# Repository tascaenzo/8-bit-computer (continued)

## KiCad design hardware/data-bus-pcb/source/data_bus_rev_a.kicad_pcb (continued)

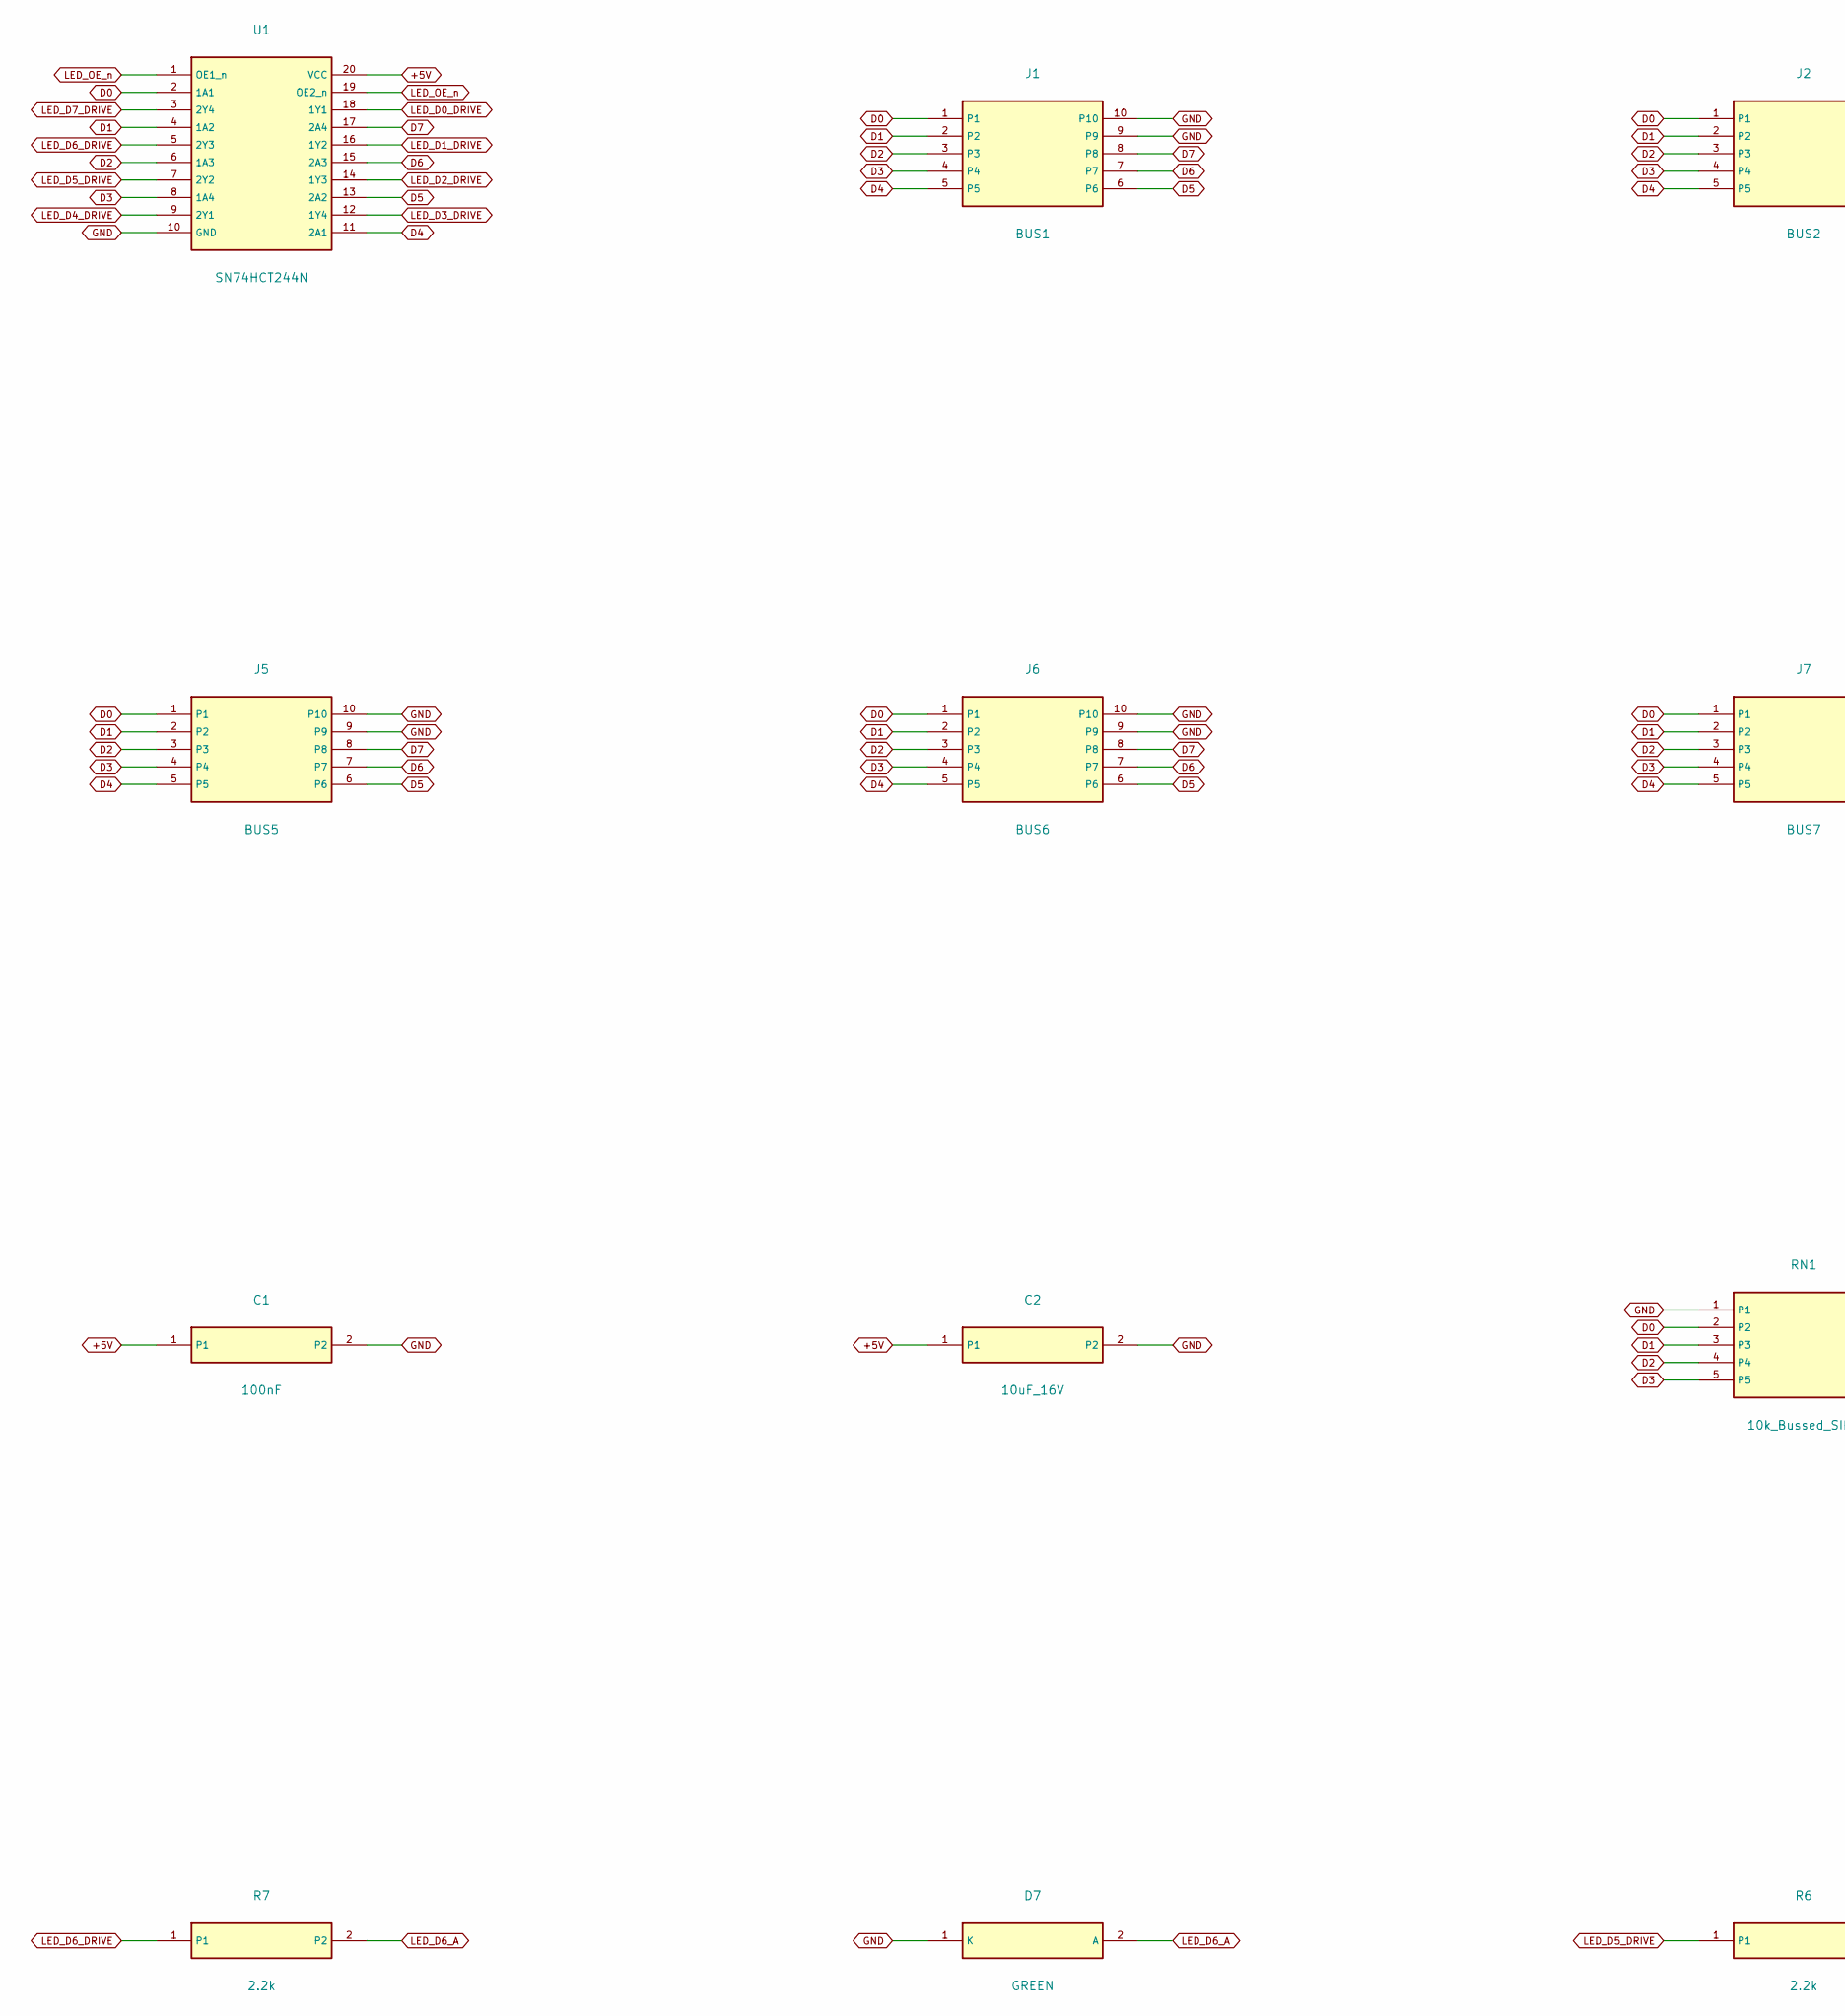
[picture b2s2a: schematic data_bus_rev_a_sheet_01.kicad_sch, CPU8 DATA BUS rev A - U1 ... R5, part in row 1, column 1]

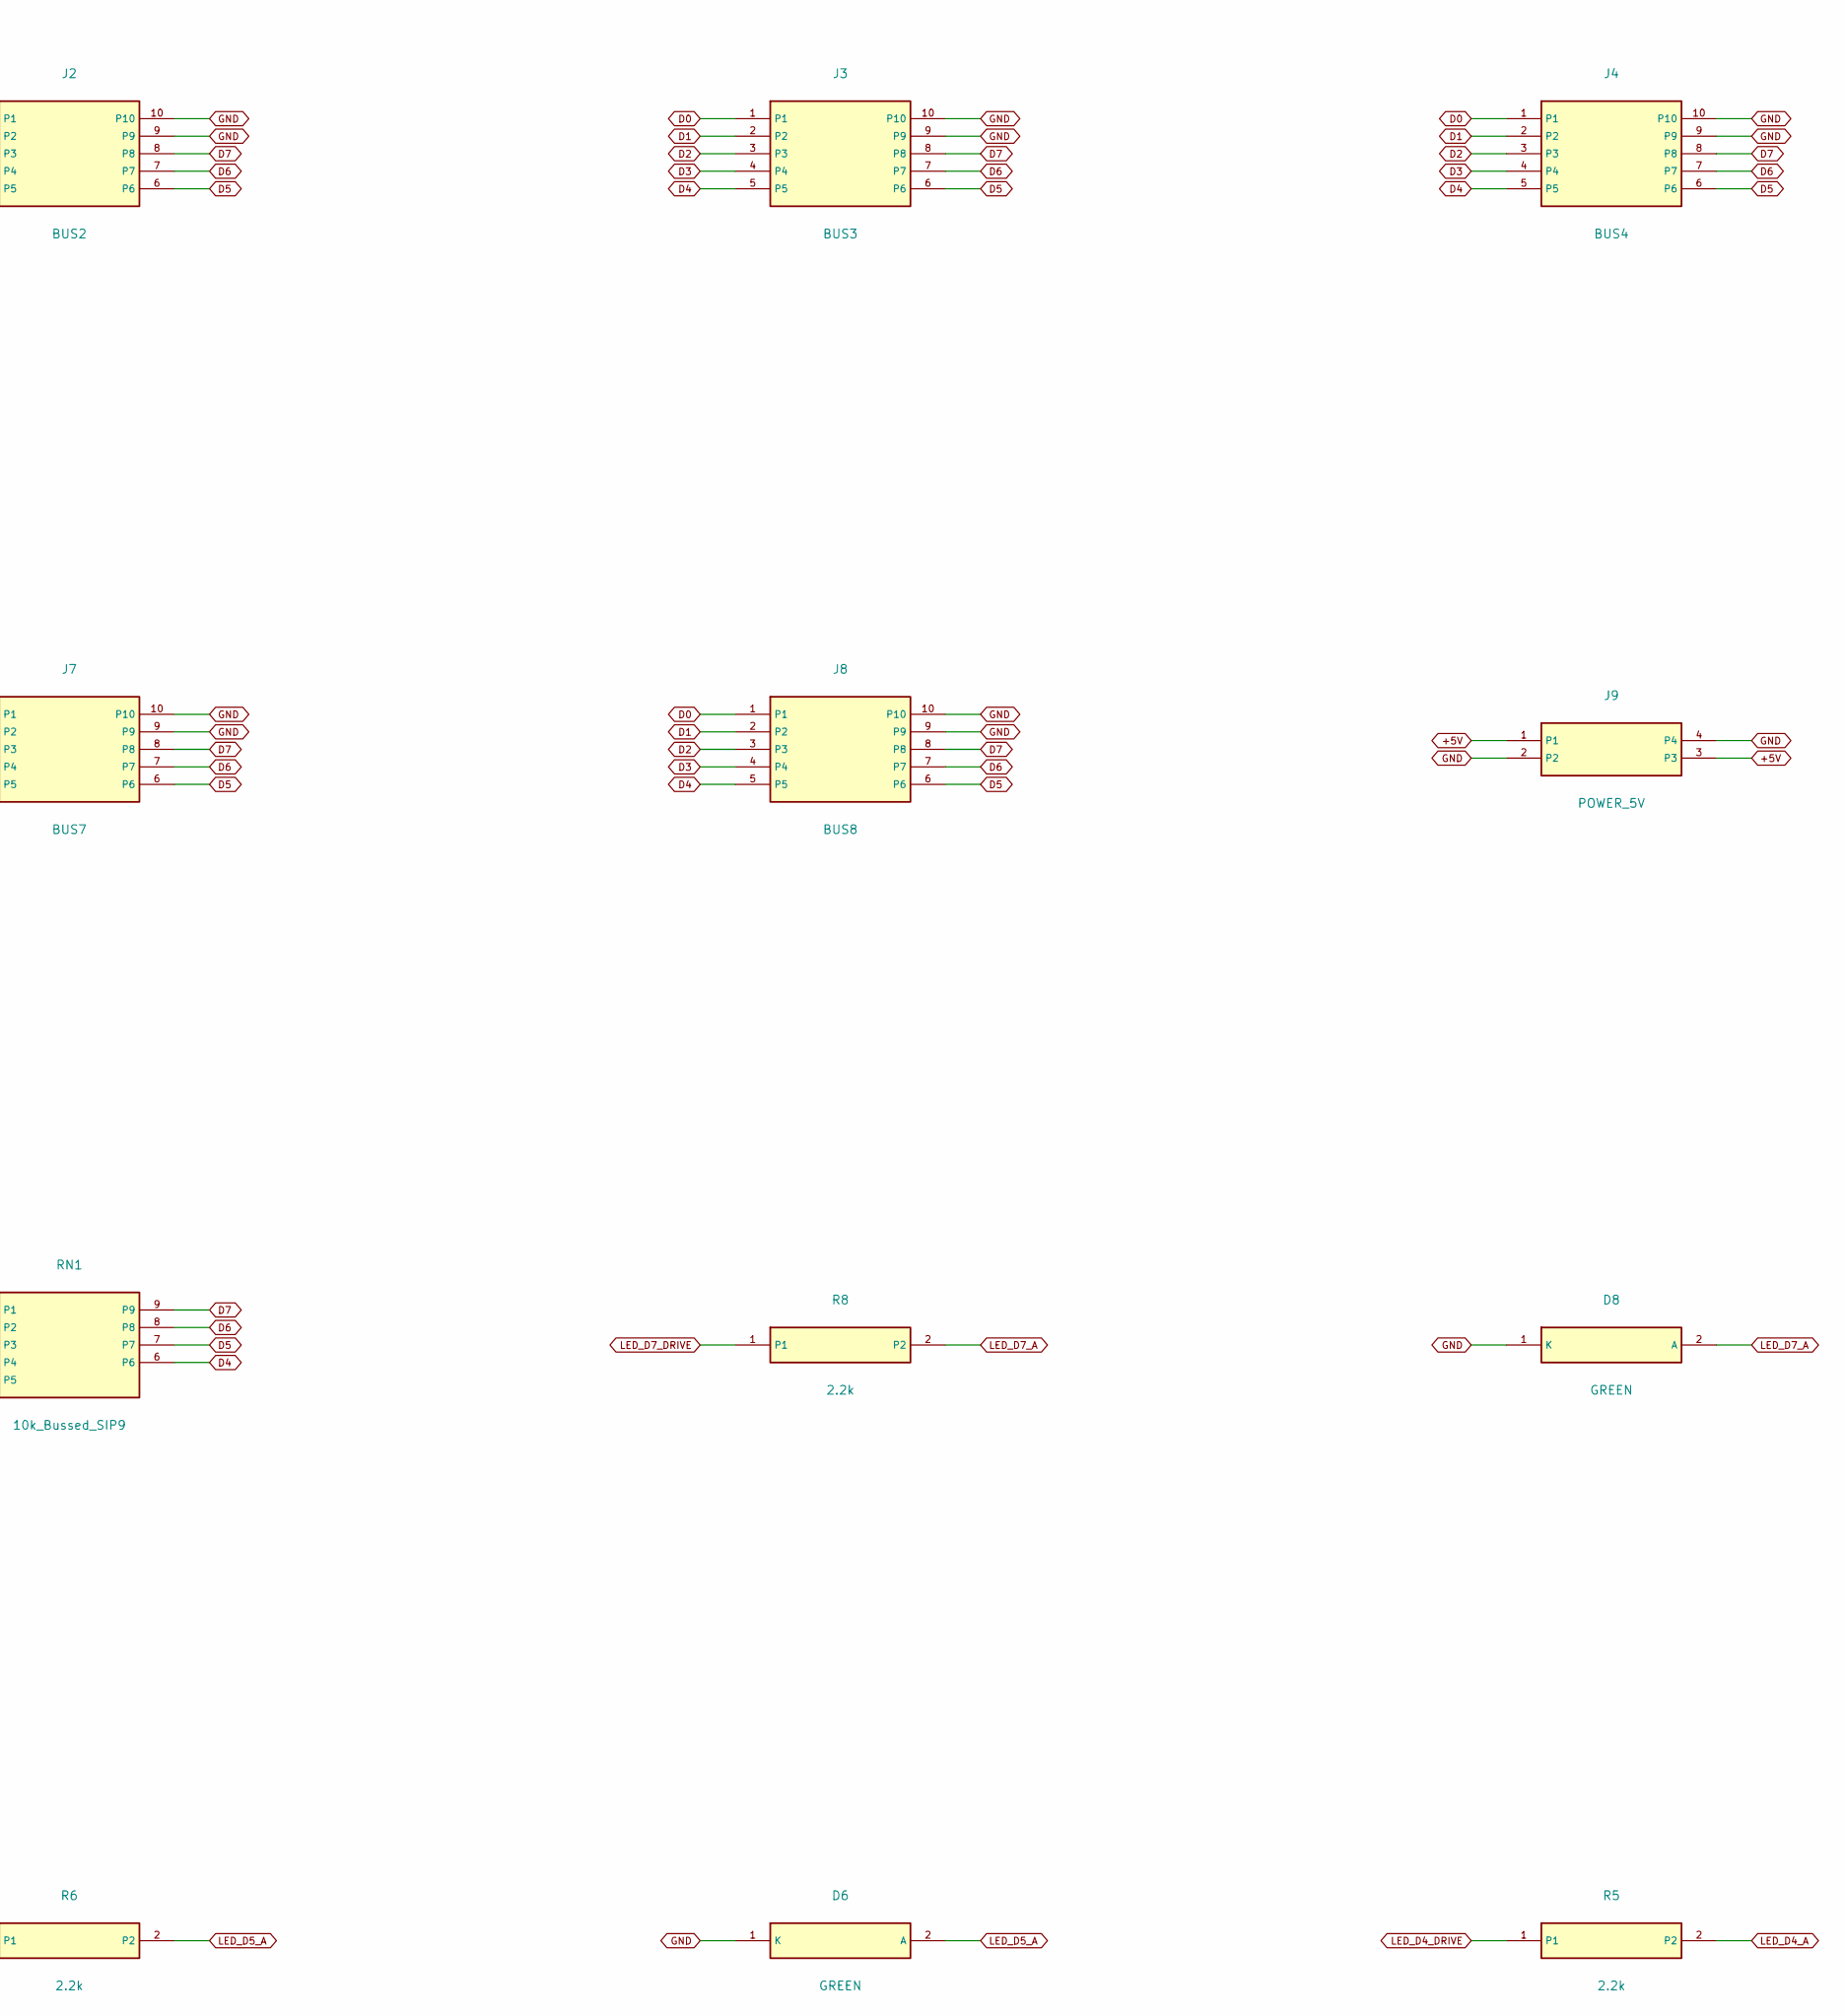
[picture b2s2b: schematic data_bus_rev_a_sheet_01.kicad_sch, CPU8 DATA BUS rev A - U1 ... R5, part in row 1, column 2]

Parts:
C1: 100nF; C_Disc_P2.50mm
C2: 10uF_16V; C_Radial_P2.50mm
D6, D7, D8: GREEN; LED_D3.0mm_P2.54mm_Vertical
J1: BUS1; Header_2x5_P2.54mm
J2: BUS2; Header_2x5_P2.54mm
J3: BUS3; Header_2x5_P2.54mm
J4: BUS4; Header_2x5_P2.54mm
J5: BUS5; Header_2x5_P2.54mm
J6: BUS6; Header_2x5_P2.54mm
J7: BUS7; Header_2x5_P2.54mm
J8: BUS8; Header_2x5_P2.54mm
J9: POWER_5V; Header_2x2_P2.54mm
R5, R6, R7, R8: 2.2k; R_Axial_P7.62mm
RN1: 10k_Bussed_SIP9; SIP-9_P2.54mm
U1: SN74HCT244N; DIP-20_W7.62mm

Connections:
+5V: C1.1, C2.1, J9.1, J9.3, U1.20 (VCC); also elsewhere on the board
D0: J1.1, J2.1, J3.1, J4.1, J5.1, J6.1, J7.1, J8.1, RN1.2, U1.2 (1A1)
D1: J1.2, J2.2, J3.2, J4.2, J5.2, J6.2, J7.2, J8.2, RN1.3, U1.4 (1A2)
D2: J1.3, J2.3, J3.3, J4.3, J5.3, J6.3, J7.3, J8.3, RN1.4, U1.6 (1A3)
D3: J1.4, J2.4, J3.4, J4.4, J5.4, J6.4, J7.4, J8.4, RN1.5, U1.8 (1A4)
D4: J1.5, J2.5, J3.5, J4.5, J5.5, J6.5, J7.5, J8.5, RN1.6, U1.11 (2A1)
D5: J1.6, J2.6, J3.6, J4.6, J5.6, J6.6, J7.6, J8.6, RN1.7, U1.13 (2A2)
D6: J1.7, J2.7, J3.7, J4.7, J5.7, J6.7, J7.7, J8.7, RN1.8, U1.15 (2A3)
D7: J1.8, J2.8, J3.8, J4.8, J5.8, J6.8, J7.8, J8.8, RN1.9, U1.17 (2A4)
GND: C1.2, C2.2, D6.1 (K), D7.1 (K), D8.1 (K), J1.9, J1.10, J2.9, J2.10, J3.9, J3.10, J4.9, J4.10, J5.9, J5.10, J6.9, J6.10, J7.9, J7.10, J8.9, J8.10, J9.2, J9.4, RN1.1, U1.10 (GND); also elsewhere on the board
LED_D0_DRIVE: U1.18 (1Y1); also elsewhere on the board
LED_D1_DRIVE: U1.16 (1Y2); also elsewhere on the board
LED_D2_DRIVE: U1.14 (1Y3); also elsewhere on the board
LED_D3_DRIVE: U1.12 (1Y4); also elsewhere on the board
LED_D4_A: R5.2; also elsewhere on the board
LED_D4_DRIVE: R5.1, U1.9 (2Y1)
LED_D5_A: D6.2 (A), R6.2
LED_D5_DRIVE: R6.1, U1.7 (2Y2)
LED_D6_A: D7.2 (A), R7.2
LED_D6_DRIVE: R7.1, U1.5 (2Y3)
LED_D7_A: D8.2 (A), R8.2
LED_D7_DRIVE: R8.1, U1.3 (2Y4)
LED_OE_n: U1.1 (OE1_n), U1.19 (OE2_n); also elsewhere on the board

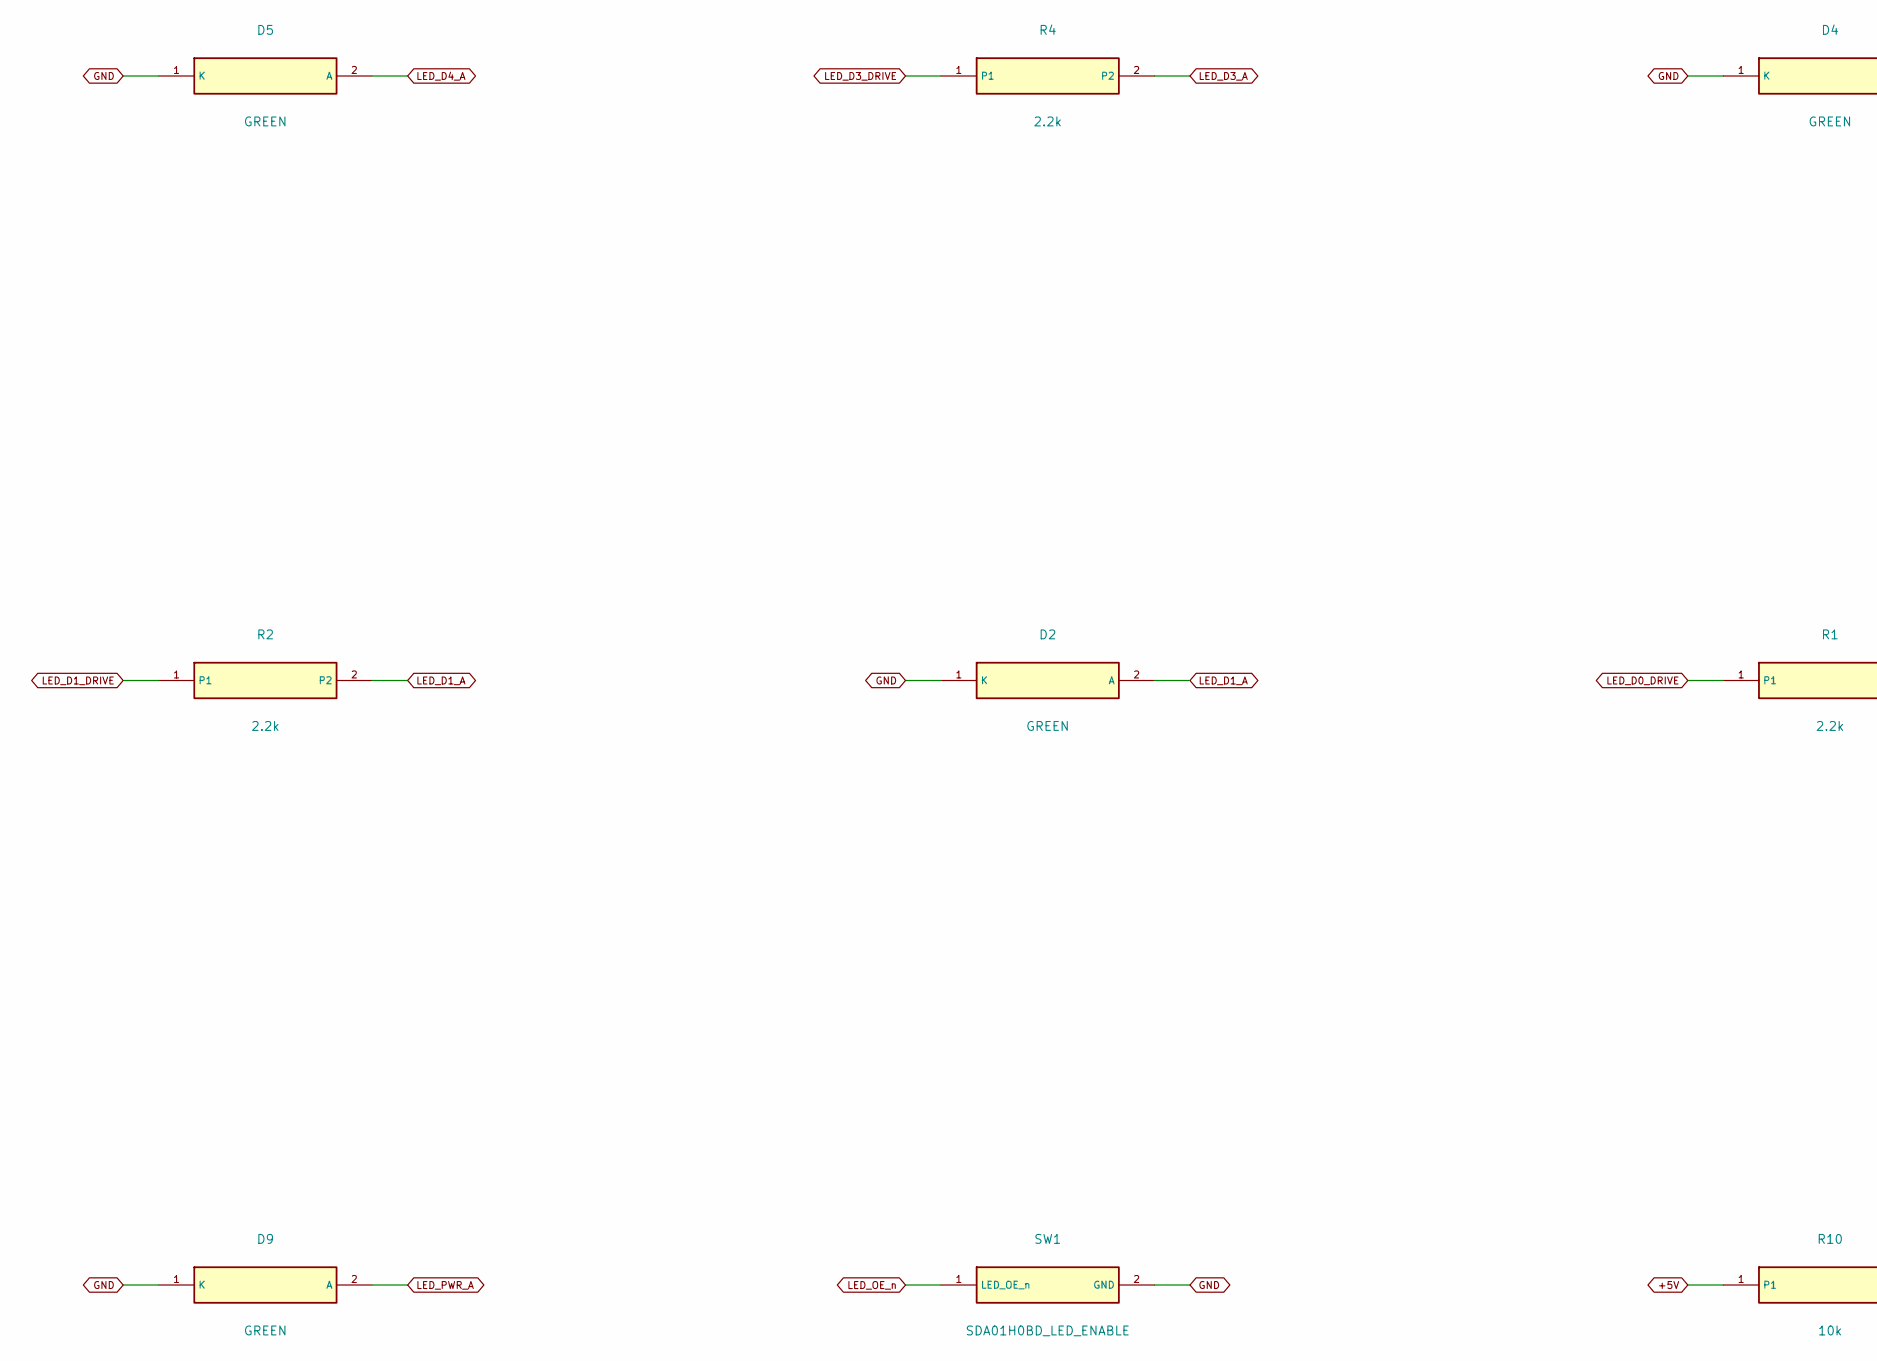
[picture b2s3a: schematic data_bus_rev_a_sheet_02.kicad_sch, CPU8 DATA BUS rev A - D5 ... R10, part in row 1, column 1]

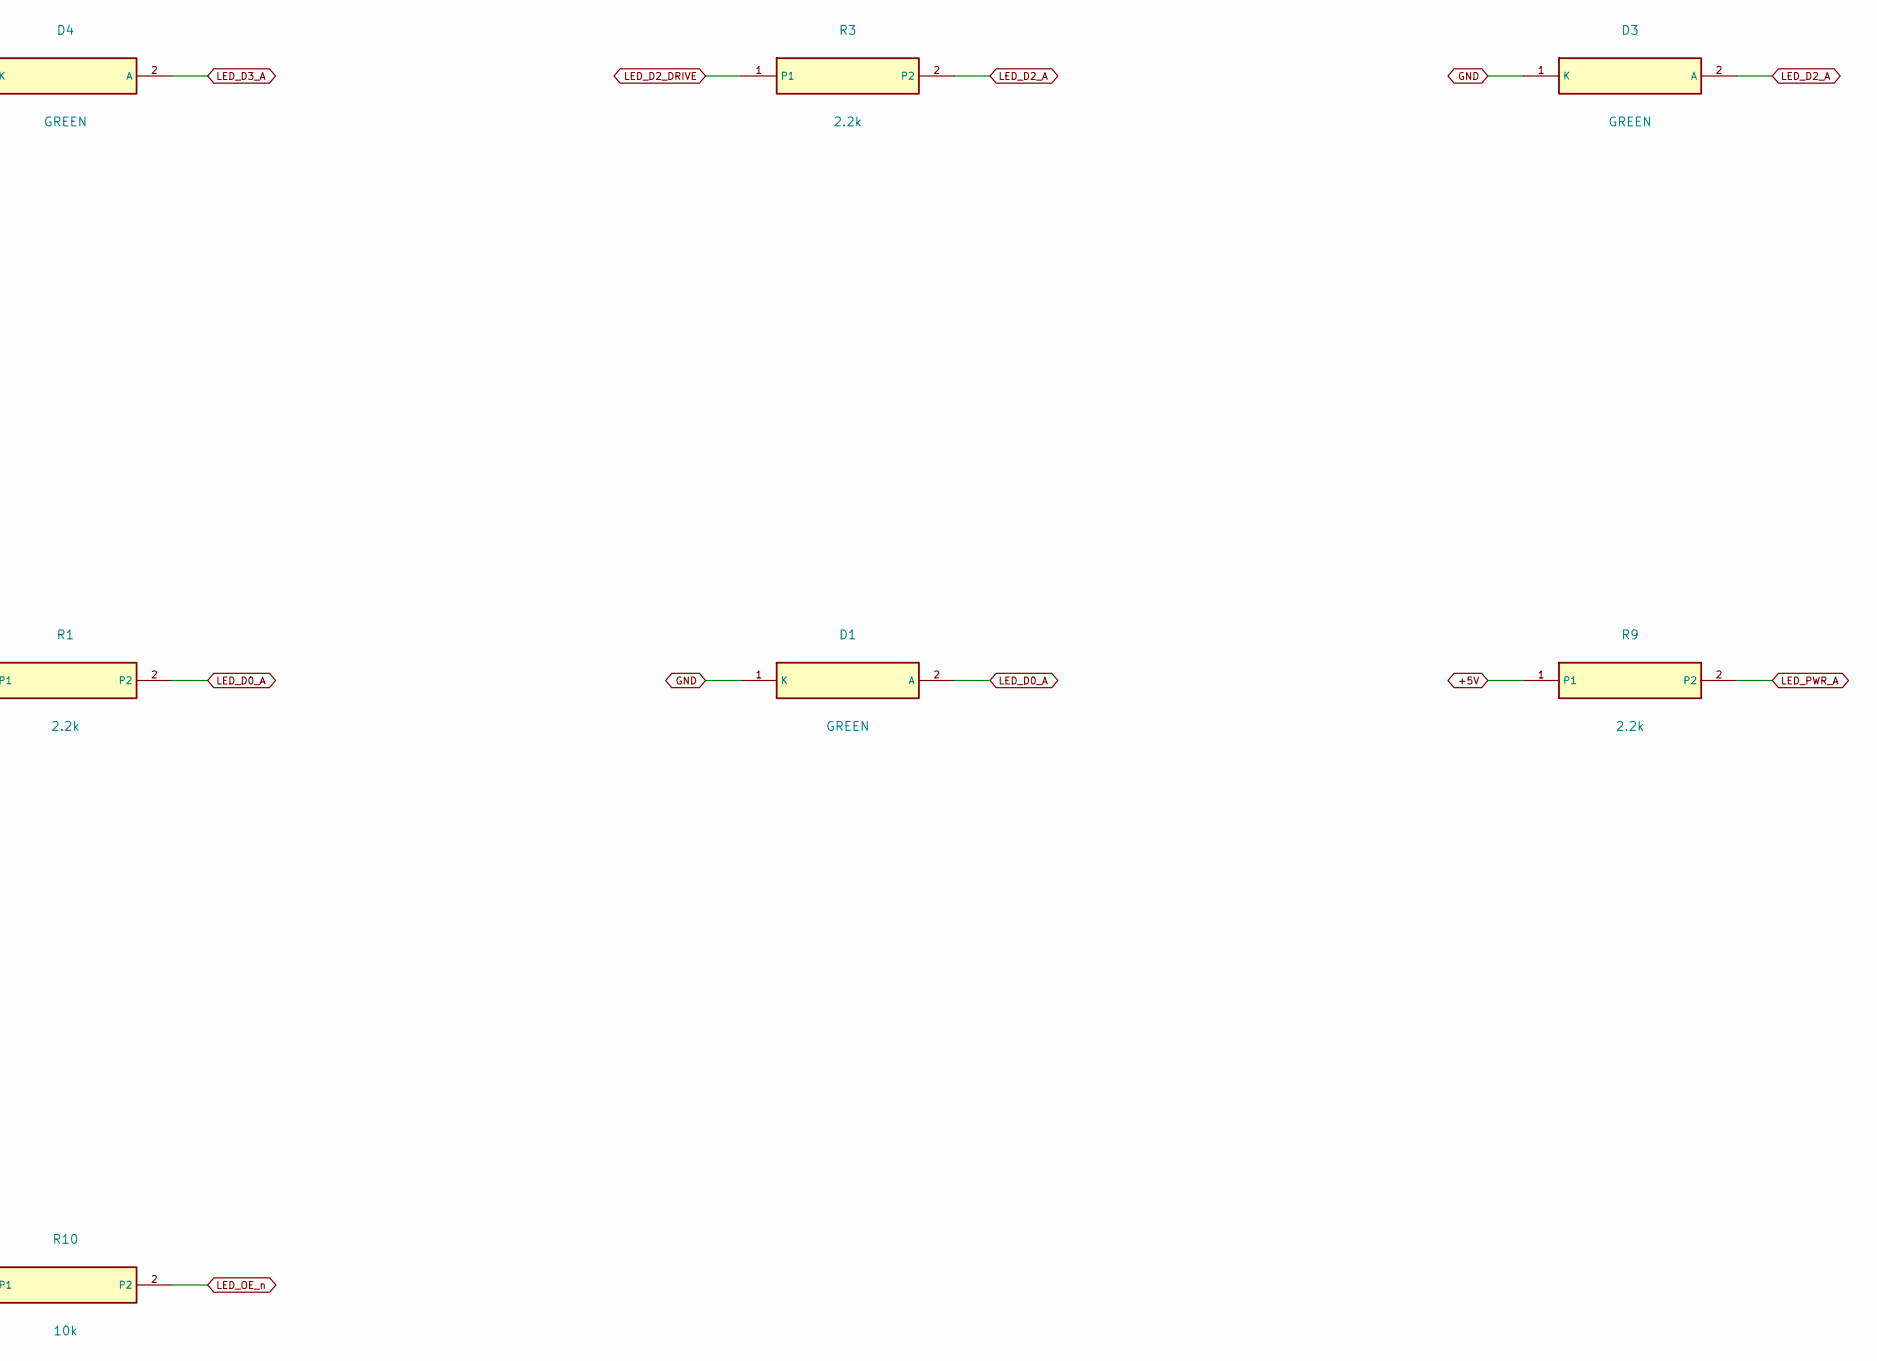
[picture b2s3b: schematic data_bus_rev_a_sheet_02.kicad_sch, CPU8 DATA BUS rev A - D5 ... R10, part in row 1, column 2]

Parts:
D1, D2, D3, D4, D5: GREEN; LED_D3.0mm_P2.54mm_Vertical
D9: GREEN; LED_D3.0mm_P2.54mm
R1, R2, R3, R4, R9: 2.2k; R_Axial_P7.62mm
R10: 10k; R_Axial_P7.62mm
SW1: SDA01H0BD_LED_ENABLE; SW_DIP_SPST_1_P2.54_W7.62

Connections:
+5V: R9.1, R10.1; also elsewhere on the board
GND: D1.1 (K), D2.1 (K), D3.1 (K), D4.1 (K), D5.1 (K), D9.1 (K), SW1.2 (GND); also elsewhere on the board
LED_D0_A: D1.2 (A), R1.2
LED_D0_DRIVE: R1.1; also elsewhere on the board
LED_D1_A: D2.2 (A), R2.2
LED_D1_DRIVE: R2.1; also elsewhere on the board
LED_D2_A: D3.2 (A), R3.2
LED_D2_DRIVE: R3.1; also elsewhere on the board
LED_D3_A: D4.2 (A), R4.2
LED_D3_DRIVE: R4.1; also elsewhere on the board
LED_D4_A: D5.2 (A); also elsewhere on the board
LED_OE_n: R10.2, SW1.1 (LED_OE_n); also elsewhere on the board
LED_PWR_A: D9.2 (A), R9.2

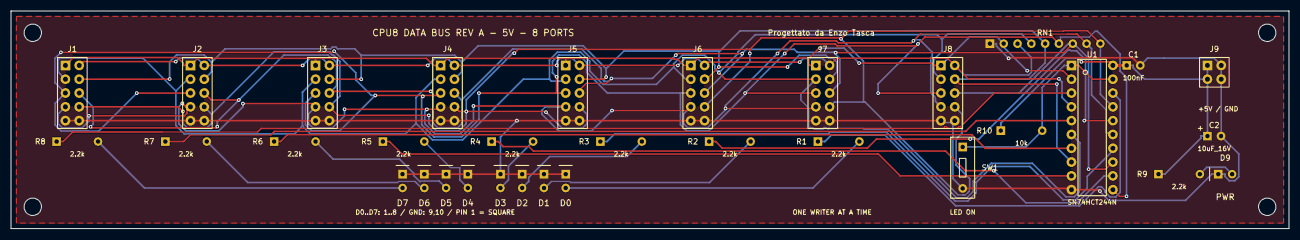
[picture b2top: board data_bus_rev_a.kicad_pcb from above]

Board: 2 copper layers, 235.0 x 40.0 mm, 33 parts (0 on the bottom side), 28 nets.

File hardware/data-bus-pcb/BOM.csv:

Reference,Value,Footprint,Purpose,Mounting_requirement
U1,SN74HCT244N,DIP-20_W7.62mm,High-impedance bus sensing; isolated LED outputs,PDIP-20; rows 7.62mm; add one DIP-20 socket
J1,BUS1,Header_2x5_P2.54mm,Bidirectional data port; ALU J4 compatible,Unshrouded 2-row male header; pitch 2.54mm
J2,BUS2,Header_2x5_P2.54mm,Bidirectional data port; ALU J4 compatible,Unshrouded 2-row male header; pitch 2.54mm
J3,BUS3,Header_2x5_P2.54mm,Bidirectional data port; ALU J4 compatible,Unshrouded 2-row male header; pitch 2.54mm
J4,BUS4,Header_2x5_P2.54mm,Bidirectional data port; ALU J4 compatible,Unshrouded 2-row male header; pitch 2.54mm
J5,BUS5,Header_2x5_P2.54mm,Bidirectional data port; ALU J4 compatible,Unshrouded 2-row male header; pitch 2.54mm
J6,BUS6,Header_2x5_P2.54mm,Bidirectional data port; ALU J4 compatible,Unshrouded 2-row male header; pitch 2.54mm
J7,BUS7,Header_2x5_P2.54mm,Bidirectional data port; ALU J4 compatible,Unshrouded 2-row male header; pitch 2.54mm
J8,BUS8,Header_2x5_P2.54mm,Bidirectional data port; ALU J4 compatible,Unshrouded 2-row male header; pitch 2.54mm
J9,POWER_5V,Header_2x2_P2.54mm,5V power; ALU J6 pinout compatible,Unshrouded 2-row male header; pitch 2.54mm
C1,100nF,C_Disc_P2.50mm,Local ceramic bypass,Ceramic 100nF 25V; pitch 2.50mm; body <=4x3mm
C2,10uF_16V,C_Radial_P2.50mm,Bulk decoupling; pin 1 positive,Electrolytic 10uF 16V; pitch 2.50mm; diameter <=5mm; pin 1 positive
RN1,10k_Bussed_SIP9,SIP-9_P2.54mm,Eight 10k bus pull-downs; common pin 1,Bussed SIP-9 8x10k; common pin 1; pitch 2.54mm
R8,2.2k,R_Axial_P7.62mm,D7 LED current limit,Axial 1/4W 5%; pitch 7.62mm; body <=6.3x2.5mm
D8,GREEN,LED_D3.0mm_P2.54mm_Vertical,Bus bit 7 indicator,3mm high efficiency LED; pitch 2.54mm; pin 1 cathode
R7,2.2k,R_Axial_P7.62mm,D6 LED current limit,Axial 1/4W 5%; pitch 7.62mm; body <=6.3x2.5mm
D7,GREEN,LED_D3.0mm_P2.54mm_Vertical,Bus bit 6 indicator,3mm high efficiency LED; pitch 2.54mm; pin 1 cathode
R6,2.2k,R_Axial_P7.62mm,D5 LED current limit,Axial 1/4W 5%; pitch 7.62mm; body <=6.3x2.5mm
D6,GREEN,LED_D3.0mm_P2.54mm_Vertical,Bus bit 5 indicator,3mm high efficiency LED; pitch 2.54mm; pin 1 cathode
R5,2.2k,R_Axial_P7.62mm,D4 LED current limit,Axial 1/4W 5%; pitch 7.62mm; body <=6.3x2.5mm
D5,GREEN,LED_D3.0mm_P2.54mm_Vertical,Bus bit 4 indicator,3mm high efficiency LED; pitch 2.54mm; pin 1 cathode
R4,2.2k,R_Axial_P7.62mm,D3 LED current limit,Axial 1/4W 5%; pitch 7.62mm; body <=6.3x2.5mm
D4,GREEN,LED_D3.0mm_P2.54mm_Vertical,Bus bit 3 indicator,3mm high efficiency LED; pitch 2.54mm; pin 1 cathode
R3,2.2k,R_Axial_P7.62mm,D2 LED current limit,Axial 1/4W 5%; pitch 7.62mm; body <=6.3x2.5mm
D3,GREEN,LED_D3.0mm_P2.54mm_Vertical,Bus bit 2 indicator,3mm high efficiency LED; pitch 2.54mm; pin 1 cathode
R2,2.2k,R_Axial_P7.62mm,D1 LED current limit,Axial 1/4W 5%; pitch 7.62mm; body <=6.3x2.5mm
D2,GREEN,LED_D3.0mm_P2.54mm_Vertical,Bus bit 1 indicator,3mm high efficiency LED; pitch 2.54mm; pin 1 cathode
R1,2.2k,R_Axial_P7.62mm,D0 LED current limit,Axial 1/4W 5%; pitch 7.62mm; body <=6.3x2.5mm
D1,GREEN,LED_D3.0mm_P2.54mm_Vertical,Bus bit 0 indicator,3mm high efficiency LED; pitch 2.54mm; pin 1 cathode
R9,2.2k,R_Axial_P7.62mm,Power LED current limit,Axial 1/4W 5%; pitch 7.62mm; body <=6.3x2.5mm
D9,GREEN,LED_D3.0mm_P2.54mm,5V supply indicator,3mm high efficiency LED; pitch 2.54mm; pin 1 cathode
SW1,SDA01H0BD_LED_ENABLE,SW_DIP_SPST_1_P2.54_W7.62,ON=bit LEDs enabled; OFF=bit LEDs disabled; power LED remains on,"C&K SDA01H0BD SPST through-hole; rows 7.62mm; pin 1 OE_n, pin 2 GND; ON closes"
R10,10k,R_Axial_P7.62mm,Pull-up disables LED buffers when SW1 is OFF,Axial 1/4W 5%; pitch 7.62mm; body <=6.3x2.5mm
